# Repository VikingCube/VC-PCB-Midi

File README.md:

https://vikingcube.com/vikingcube/vikingcube-midi/

# VikingCube Midi PCB Repository
This repository has the KiCad files for making the PCBs for the VikingCube Midi.

~ is a 4 channel USB Midi to CV modular synth module. Features CV, Gate and Velocity outputs for all 4 channels, and gives you 4 note poly on Midi CH5.

The firmware lives in a separeted repository for the atmega32u4.

# Legal
You are free to download, build, modify VikingCube Midi with absolutely no fee and any kind of guarantee. We believe in the mindset of opensource - if you like please
mark the source with references for this repositroy or our website: www.vikingcube.com

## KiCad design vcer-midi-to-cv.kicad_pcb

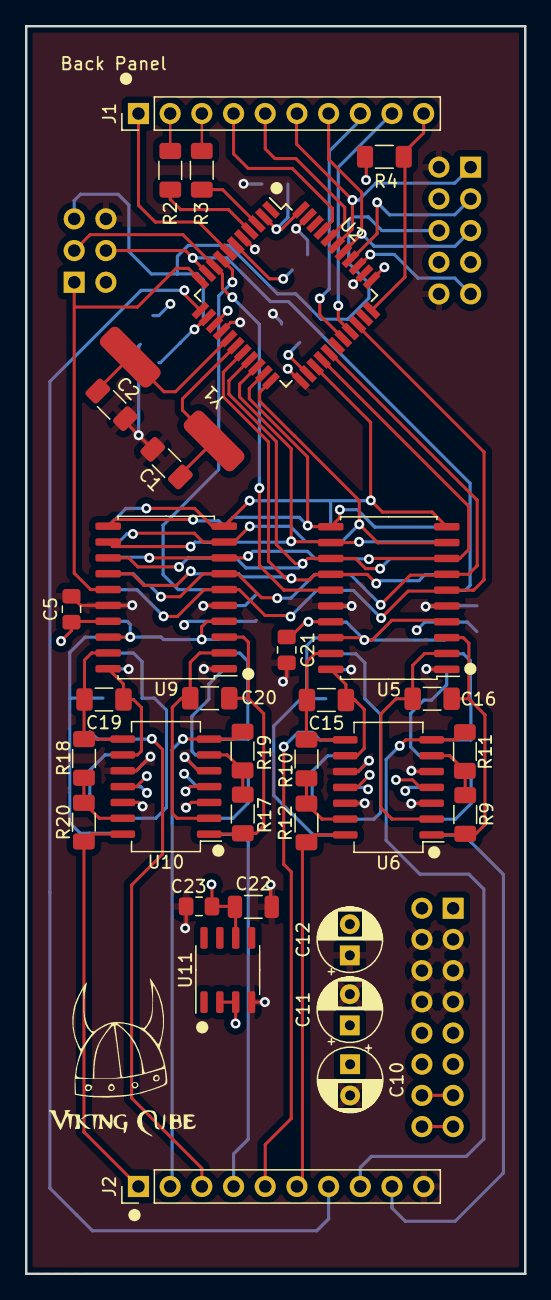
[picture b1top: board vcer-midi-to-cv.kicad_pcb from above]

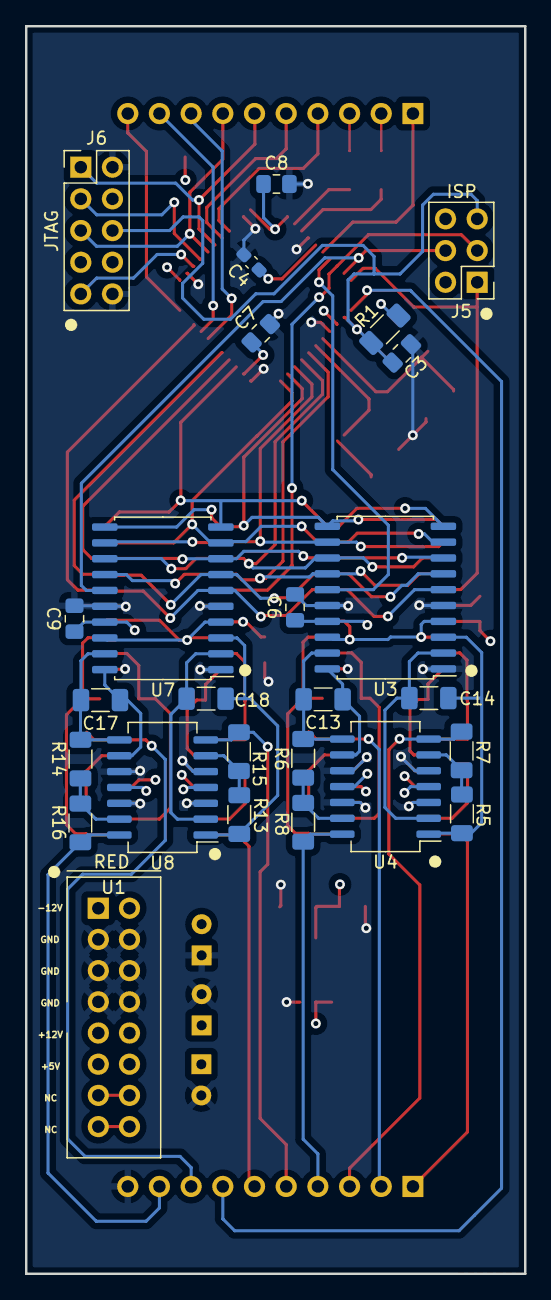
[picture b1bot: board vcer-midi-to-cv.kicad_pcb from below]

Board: 4 copper layers, 40.0 x 100.0 mm, 59 parts (26 on the bottom side), 69 nets.

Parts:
C1, C2: 18pF; C_1206_3216Metric_Pad1.33x1.80mm_HandSolder
C3, C5, C6, C7, C8, C9, C21: 100nF; C_0805_2012Metric_Pad1.18x1.45mm_HandSolder
C4: 1u; C_0603_1608Metric_Pad1.08x0.95mm_HandSolder
C10, C11, C12: 100uF; CP_Radial_D5.0mm_P2.50mm
C13, C14, C15, C16, C17, C18, C19, C20: 15pF; C_1206_3216Metric_Pad1.33x1.80mm_HandSolder
C22: 1uF (TANT); C_1206_3216Metric
C23: 100nF (Ceramic); C_0805_2012Metric_Pad1.18x1.45mm_HandSolder
J1, J2: Conn_01x10_Male; PinHeader_1x10_P2.54mm_Vertical
J5: AVR-ISP-6; PinHeader_2x03_P2.54mm_Vertical
J6: AVR-JTAG-10; PinHeader_2x05_P2.54mm_Vertical
R1, R4: 10k; R_1206_3216Metric_Pad1.30x1.75mm_HandSolder
R2, R3: 22; R_1206_3216Metric_Pad1.30x1.75mm_HandSolder
R5, R6, R7, R8, R9, R10, R11, R12, R13, R14, R15, R16, R17, R18, R19, R20: R-10k-1206; R_1206_3216Metric_Pad1.30x1.75mm_HandSolder
U1: power_conn_16; power_16
U2: ATmega32U4-A; TQFP-44_10x10mm_P0.8mm
U3, U5, U7, U9: TLC7528; SOIC-20W_7.5x12.8mm_P1.27mm
U4, U6, U8, U10: TL074; SO-14_5.3x10.2mm_P1.27mm
U11: REF195; SO-8_3.9x4.9mm_P1.27mm
Y1: 16Mhz; HC49-4HSMX

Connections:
+5F: C22.1, C23.1, U3.4 (REFA), U3.18 (REFB), U5.4 (REFA), U5.18 (REFB), U7.4 (REFA), U7.18 (REFB), U9.4 (REFA), U9.18 (REFB), U11.6 (Vout)
+5V: C5.1, C6.1, C7.1, C8.1, C9.1, C10.1, C21.1, J5.2 (VCC), J6.4 (VREF), R1.1, R4.1, U1.11 (+5V), U1.12 (+5V), U2.2 (UVCC), U2.14 (VCC), U2.24 (AVCC), U2.34 (VCC), U2.44 (AVCC), U3.17 (Vdd), U5.17 (Vdd), U7.17 (Vdd), U9.17 (Vdd)
+12V: C11.1, U1.9 (+12V), U1.10 (+12V), U4.4 (V+), U6.4 (V+), U8.4 (V+), U10.4 (V+), U11.2 (Vin), U11.3 (~Sleep)
-12V: C12.2, U1.1 (-12V), U1.2 (-12V), U4.11 (V-), U6.11 (V-), U8.11 (V-), U10.11 (V-)
/CS1: U2.8 (PB0), U3.15 (_CS)
/CS2: J5.3 (SCK), U2.9 (PB1), U5.15 (_CS)
/CS3: J5.4 (MOSI), U2.10 (PB2), U7.15 (_CS)
/CS4: J5.1 (MISO), U2.11 (PB3), U9.15 (_CS)
/CV1: J2.3, R7.2, U4.7
/CV2: J2.4, R8.2, U4.14
/CV3: J2.8, R11.2, U6.7
/CV4: J2.6, R12.2, U6.14
/D0: U2.18 (PD0), U3.14 ((LSB)_DB0), U5.14 ((LSB)_DB0), U7.14 ((LSB)_DB0), U9.14 ((LSB)_DB0)
/D1: U2.19 (PD1), U3.13 (DB1), U5.13 (DB1), U7.13 (DB1), U9.13 (DB1)
/D2: U2.20 (PD2), U3.12 (DB2), U5.12 (DB2), U7.12 (DB2), U9.12 (DB2)
/D3: U2.21 (PD3), U3.11 (DB3), U5.11 (DB3), U7.11 (DB3), U9.11 (DB3)
/D4: U2.25 (PD4), U3.10 (DB4), U5.10 (DB4), U7.10 (DB4), U9.10 (DB4)
/D5: U2.22 (PD5), U3.9 (DB5), U5.9 (DB5), U7.9 (DB5), U9.9 (DB5)
/D6: U2.26 (PD6), U3.8 (DB6), U5.8 (DB6), U7.8 (DB6), U9.8 (DB6)
/D7: U2.27 (PD7), U3.7 ((MSB)_DB7), U5.7 ((MSB)_DB7), U7.7 ((MSB)_DB7), U9.7 ((MSB)_DB7)
/D+: J1.2, R2.2
/D-: J1.3, R3.2
/DACA/B: U2.31 (PC6), U3.6 (_DACA/DACB), U5.6 (_DACA/DACB), U7.6 (_DACA/DACB), U9.6 (_DACA/DACB)
/G1: J1.4, U2.41 (PF0)
/G2: J1.5, U2.40 (PF1)
/G3: J1.6, J6.1 (TCK), U2.39 (PF4)
/G4: J1.7, J6.5 (TMS), U2.38 (PF5)
/L1: J1.8, U2.29 (PB5)
/L2: J1.9, U2.30 (PB6)
/L3: J2.7, U2.12 (PB7)
/PRG: J1.10, R4.2, U2.33 (~HWB/PE2)
/TDI: J6.9 (TDI), U2.36 (PF7)
/TDO: J6.3 (TDO), U2.37 (PF6)
/VBUS: J1.1, U2.7 (VBUS)
/Vel1: J2.5, R15.2, U8.7
/Vel2: J2.9, R16.2, U8.14
/Vel3: J2.2, R19.2, U10.7
/Vel4: J2.1, R20.2, U10.14
/reset: C3.1, J5.5 (~RST), J6.6 (~SRST), R1.2, U2.13 (~RESET)
GND: C1.2, C2.2, C3.2, C4.2, C5.2, C6.2, C7.2, C8.2, C9.2, C10.2, C11.2, C12.1, C21.2, C22.2, C23.2, J2.10, J5.6 (GND), J6.2 (GND), J6.10 (GND), U1.3 (GND), U1.4 (GND), U1.5 (GND), U1.6 (GND), U1.7 (GND), U1.8 (GND), U2.5 (UGND), U2.15 (GND), U2.23 (GND), U2.35 (GND), U2.43 (GND), U3.1 (AGND), U3.5 (DGND), U3.16 (_WR), U4.3 (+), U4.5 (+), U4.10 (+), U4.12 (+), U5.1 (AGND), U5.5 (DGND), U5.16 (_WR), U6.3 (+), U6.5 (+), U6.10 (+), U6.12 (+), U7.1 (AGND), U7.5 (DGND), U7.16 (_WR), U8.3 (+), U8.5 (+), U8.10 (+), U8.12 (+), U9.1 (AGND), U9.5 (DGND), U9.16 (_WR), U10.3 (+), U10.5 (+), U10.10 (+), U10.12 (+), U11.4 (GND)
unnamed: C1.1, U2.17 (XTAL1), Y1.1
unnamed: C2.1, U2.16 (XTAL2), Y1.2
unnamed: C4.1, U2.6 (UCAP)
unnamed: C13.1, U3.20 (OUTB), U4.9 (-)
unnamed: C13.2, R6.1, U3.19 (RFBB), U4.8
unnamed: C14.1, R5.1, U3.3 (RFBA), U4.1
unnamed: C14.2, U3.2 (OUTA), U4.2 (-)
unnamed: C15.1, U5.20 (OUTB), U6.9 (-)
unnamed: C15.2, R10.1, U5.19 (RFBB), U6.8
unnamed: C16.1, R9.1, U5.3 (RFBA), U6.1
unnamed: C16.2, U5.2 (OUTA), U6.2 (-)
unnamed: C17.1, U7.20 (OUTB), U8.9 (-)
unnamed: C17.2, R14.1, U7.19 (RFBB), U8.8
unnamed: C18.1, R13.1, U7.3 (RFBA), U8.1
unnamed: C18.2, U7.2 (OUTA), U8.2 (-)
unnamed: C19.1, U9.20 (OUTB), U10.9 (-)
unnamed: C19.2, R18.1, U9.19 (RFBB), U10.8
unnamed: C20.1, R17.1, U9.3 (RFBA), U10.1
unnamed: C20.2, U9.2 (OUTA), U10.2 (-)
unnamed: R2.1, U2.4 (D+)
unnamed: R3.1, U2.3 (D-)
unnamed: R5.2, R7.1, U4.6 (-)
unnamed: R6.2, R8.1, U4.13 (-)
unnamed: R10.2, R12.1, U6.13 (-)
unnamed: R9.2, R11.1, U6.6 (-)
unnamed: R13.2, R15.1, U8.6 (-)
unnamed: R14.2, R16.1, U8.13 (-)
unnamed: R17.2, R19.1, U10.6 (-)
unnamed: R18.2, R20.1, U10.13 (-)

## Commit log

2022-11-01 Added README.md
2022-11-26 I have some changes, but no idea what
2022-12-03 recovered the cover plate from the old version - I declare v2.0 here by
2022-12-06 fixed mounting holes
2022-12-06 removed other panels
